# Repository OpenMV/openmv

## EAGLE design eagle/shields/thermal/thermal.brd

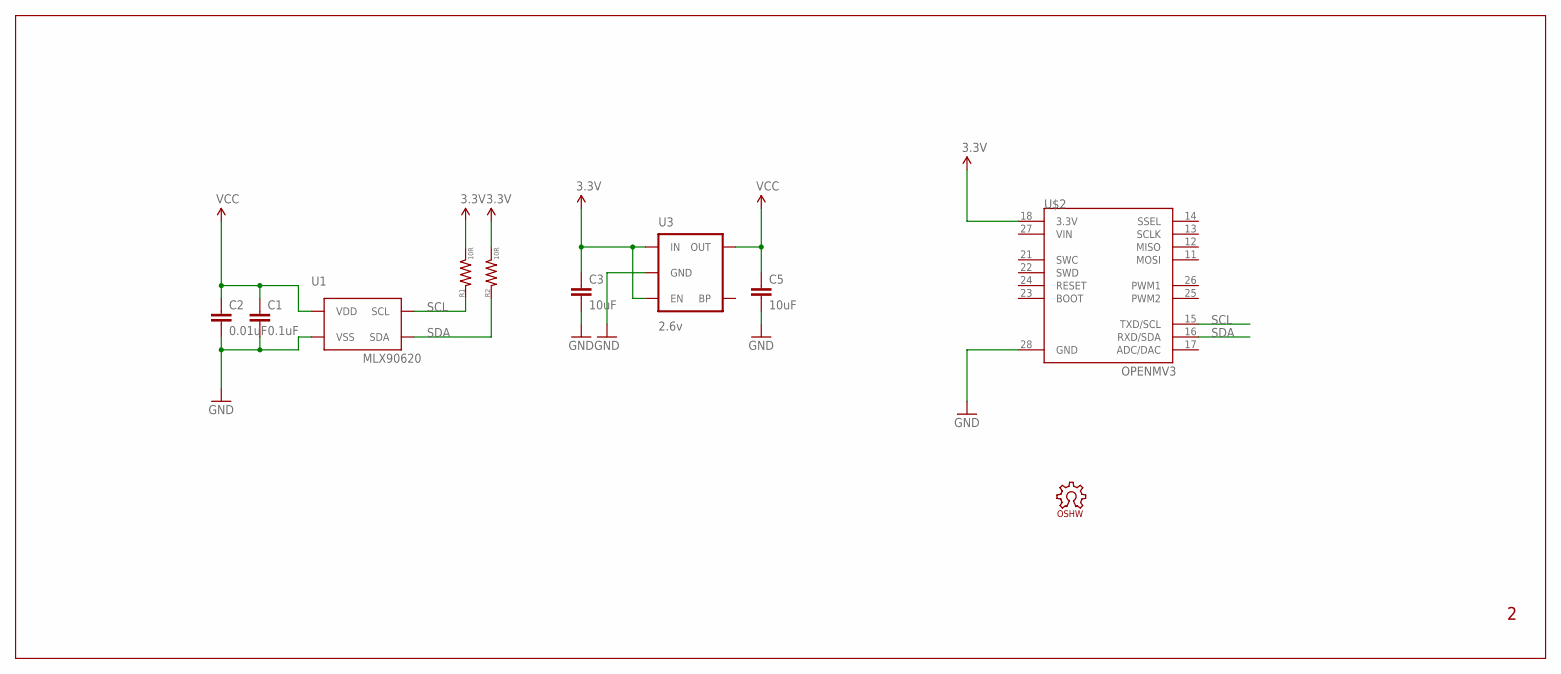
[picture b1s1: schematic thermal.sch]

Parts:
C1: 0.1uF; 0603-CAP
C2: 0.01uF; 0603-CAP
C3, C5: 10uF; 0805
LOGO1: OSHW_LOGO_8MILX0150-NT; OSHW_8X150_NOTEXT
R1, R2: 10R; 0603-RES
U1: MLX90620; TO39/4
U3: 2.6v; SOT23-5
U$2: OPENMV3

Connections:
3.3V: C3.1, R1.1, R2.1, U3.1 (IN), U3.3 (EN), U$2.18 (3.3V)
GND: C1.2, C2.2, C3.2, C5.2, U1.4 (VSS), U3.2 (GND), U$2.28 (GND)
SCL: R1.2, U1.1 (SCL), U$2.15 (TXD/SCL)
SDA: R2.2, U1.2 (SDA), U$2.16 (RXD/SDA)
VCC: C1.1, C2.1, C5.1, U1.3 (VDD), U3.5 (OUT)
VIN: U$2.27 (VIN)

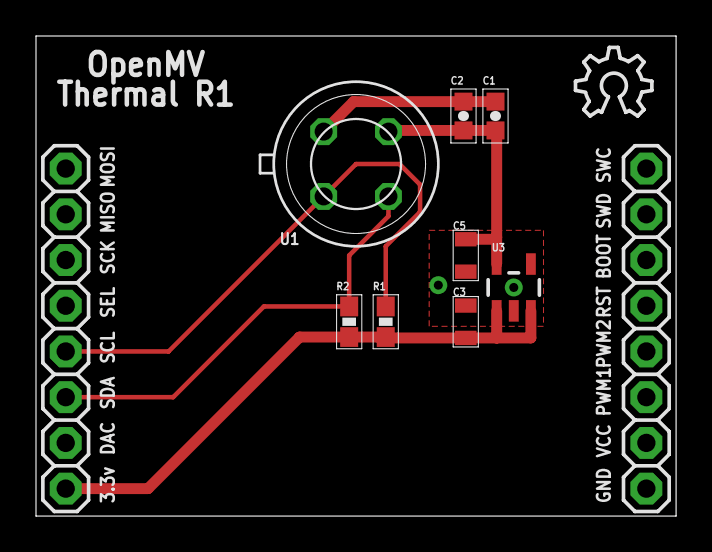
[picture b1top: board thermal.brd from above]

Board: 2 copper layers, 35.6 x 26.7 mm, 10 parts (0 on the bottom side), 5 nets.

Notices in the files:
eagle/shields/thermal/thermal.sch:
Copyright (c) 2013 Ibrahim Abd Elkader
This work is licensed under the Creative Commons Attribution-ShareAlike 3.0 License.
To view a copy of this license, visit http://creativecommons.org/licenses/by-sa/3.0
